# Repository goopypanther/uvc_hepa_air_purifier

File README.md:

# Air Purifier

This design was inspired by kels316's [DIY Air Purifier](https://github.com/Kels316/DIY-Air-Purifier/) and numerous other xiaomi derived air purifier designs available on thingiverse.

I didn't have easy access to the specific cylindrical HEPA filter and this design was originally intended to simply accept a different size. I went on to add UV sterilization to more closely feature-match an old commercial filtration unit which required replacement.

UV sterilization is provided by a 3W GTL3 UVC bulb which may also produce small amounts of ozone (depending on envelope coatings). This is ballasted by a capacitive dropper which provides the bulb ~10VAC at a couple hundred milliamps.

GTL3 bulbs have an interesting self-ignition design, they initially operate as a thermionic emitter using a filament with a negative thermal coefficient until a sufficient mercury plasma is generated in the envelope. The plasma cloud then conducts the majority of the current once the filament reaches a high-resistance state. AC operation is preferred over DC to prevent premature erosion of one end of the filament.

Airflow is provided by an inexpensive computer case fan operating at 12V. Due to the simplicity of the circuit and inherent safety of a fully enclosed device another capacitive dropper is used, followed by a full bridge rectifier and zener for rough regulation.

Both capacitive droppers have bleeder resistors in parallel with the class X capacitors to prevent shocks off the end of the cable. The 120VAC input is protected with a fuse, MOV and inrush current limiter. I chose to install an in-line switch into the power cable but this is optional.

In order to maximize the exposure of the air-stream to UVC radiation the area immediately surrounding the GTL3 bulb is sheathed in aluminum foil which will reflect the radiation through the chamber multiple times as well as protect the plastic from degradation. Other surfaces of the baffle are painted with white (titanium dioxide) interior house paint for protection. According to the scientific literature TiO is an efficient absorber of UVC radiation and should reduce the amount which escapes through the baffle via reflection. It also photocatalytically destroys VOCs but I'm not clear on if a paint coating has this ability or if it requires special preparation of the TiO particles.

I also posted an explanitory video of the build process [on youtube.](https://www.youtube.com/watch?v=l4DuUhZftfQ)

## File Structure

```
cad    -- FreeCAD 0.19 design documents using Assembly4 workbench
          Top level assembly document 0_top_level_uvc_air_filter.FCStd
stl    -- Exported models for 3D printing

PCB    -- Power supply PCB design files and BOM
gerber -- Zipped gerber files for PCB fabhouse
sim    -- ltspice simulation of power supply
```

## Bill Of Materials

| Qty | Part                           | Link                                                                     |
|-----|--------------------------------|--------------------------------------------------------------------------|
| 1   | PSU PCB                        | Fab from gerbers/BOM                                                     |
| 1   | Air Filter                     | https://www.amazon.com/gp/product/B08245MH67/ or similar 88mm dia filter |
| 4   | Vibration dampening fan rivets | https://www.amazon.com/gp/product/B00H9905KA/ or similar                 |
| 1   | GTL3 Bulb                      | https://www.amazon.com/gp/product/B081RSZT6S/ or similar                 |
| 1   | E17 Socket                     | https://www.amazon.com/gp/product/B07J4ZTYWZ/ or similar                 |
| 23  | M3 Nut                         | https://www.mcmaster.com/90592A085/ or similar                           |
| 21  | M3x16 Bolt                     | https://www.mcmaster.com/91290A120/ or similar                           |
| 2   | M3x8 Bolt (For E17 socket)     | https://www.mcmaster.com/91290A113/ or similar                           |
| 2   | M3 Washer (For E17 socket)     | https://www.mcmaster.com/91166a210/ or similar                           |
| 1   | Power Cable                    | https://www.mcmaster.com/7248K21/ or similar                             |
| 1   | Inline Switch (Optional)       | https://www.mcmaster.com/14695K91/ or similar                            |
| 1   | 120mm Fan                      | Purchase or recycle from PC                                              |
| 1   | Aluminum Foil                  | Purchase                                                                 |
| 2   | Zipties (For Power Cable)      | Purchase                                                                 |
| 4   | M3x5 Standoff                  | 3D Print or purchase                                                     |
| 3   | Foot                           | 3D Print in TPU or purchase compatible feet                              |
| 1   | Upper Baffle                   | 3D Print                                                                 |
| 1   | Top Cap                        | 3D Print                                                                 |
| 1   | Lower Baffle                   | 3D Print                                                                 |
| 1   | Fan Cover                      | 3D Print                                                                 |
| 1   | Bottom Cap                     | 3D Print                                                                 |
| 1   | Baffle Cap Bracket             | 3D Print                                                                 |
| 1   | Baffle Cap                     | 3D Print                                                                 |

## Assembly Notes

The supplied gerber zip file is submittable to JLCPCB/OSHPARK or other PCB fabhouse. It is important that the AC series capacitors are at least class X1 to prevent blown fuses or fire. Take care when testing this circuit, the outputs float and may have a 120VAC potential to ground so don't touch it! It may also destroy non-isolated oscilloscopes or other ground-referenced test equipment. UVC light is dangerous to the eyes and causes skin cancer, damages plastic and will even kill houseplants with sufficient exposure. Don't stare at the bulb, only run open-air tests briefly and preferably view it through the screen of a digital camera or UV filtered glasses.

Total 3D printing time on my ender 3 with 20% infill was about 75 hours and used approximately 500g of filament.

Coat innermost surfaces of Bottom Cap with TiO paint, as well as outer surfaces of Upper and Lower Baffle and inner surfaces of Baffle Cap.

For ease of construction build the Internal Baffle Assembly first and glue aluminum foil to its inner surface. Then assemble into Top Cap.

Build Bottom Cap Assembly and Fan Cover Assembly as independent units. Ensure fan blows air outward through the vent holes. When screwing feet into Bottom Cap ensure the bolts do not sit excessively proud of the Bottom Cap surface where they would interfere with the filter's foam seal.

When building Baffle Cap Assembly start by installing the Baffle Cap Bracket, then the E17 Socket. The E17 mounting holes were oversized and required washers. Feed E17 wires through the holes in the Baffle Cap and Bracket before installing fasteners. Use short bolts to leave room on rear face for the PCB. The two captive nut features on the top face of the Baffle Cap were tight but the nuts seated as the bolts were screwed in. Afterward the PCB can be installed with the standoffs and the E17 wires can be connected. At that point the GTL3 bulb can be screwed into the socket and the assembly can be attached to the Top Cap.

For stability the Bottom Cap Assembly, Filter and Top Cap Assembly can be fit together before wiring the Power Cable. Plug the fan into the PCB and carefully slot the power cable into the mouse-hole on the edge of the Fan Cover. With the Fan Cover seated over the Top Cap a ziptie can be applied to the cable up against the cover to prevent it from being pushed inside the unit. The Fan Cover can then be temporarily removed to install a second ziptie on the cable against the inner surface of the Fan Cover to prevent the cable from being pulled out of the PCB. The Fan Cover can then be screwed into the Top Cap taking care that the bolts do not sit excessively proud of the surface where they would interfere with the filter's foam seal.

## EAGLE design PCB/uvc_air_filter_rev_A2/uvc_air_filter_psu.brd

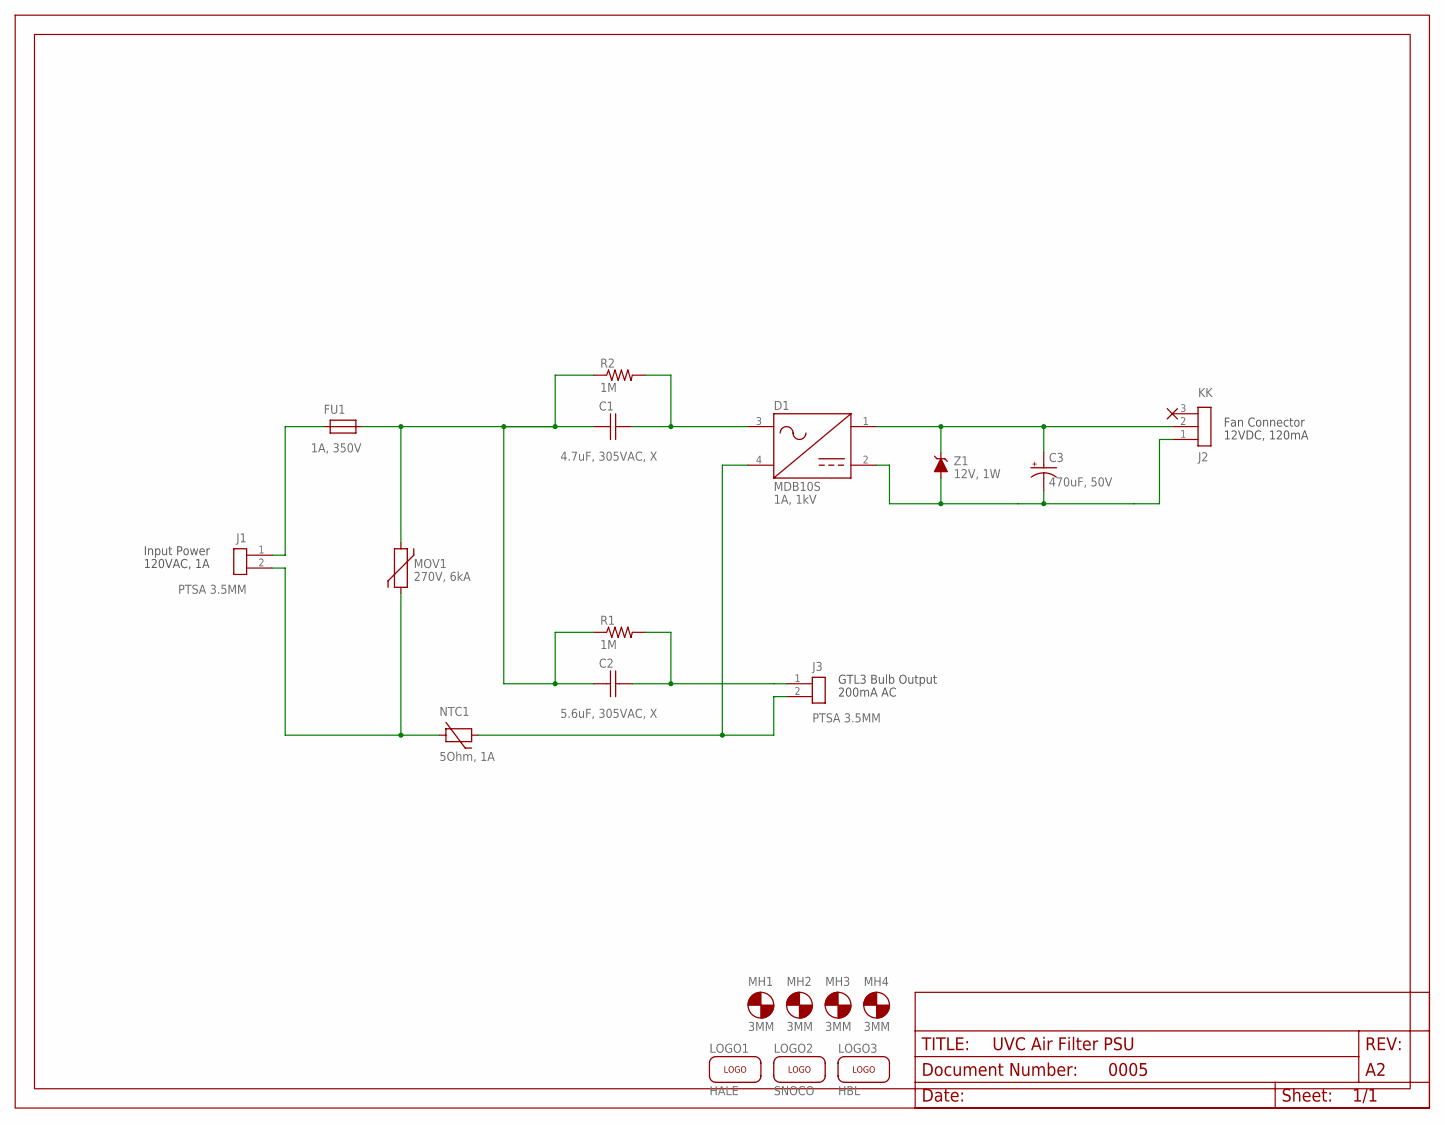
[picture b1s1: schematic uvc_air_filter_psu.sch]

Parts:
C1: 4.7uF, 305VAC, X; CAP-27.5MM
C2: 5.6uF, 305VAC, X; CAP-27.5MM
C3: 470uF, 50V; CAP-5MM-10MM; DIGIKEY P5185-ND
D1: 1A, 1kV; TSSOP-4
FU1: 1A, 350V; FUSE-5X15MM
J1, J3: PTSA 3.5MM; HEADER-PTSA-3.5MM-1X2
J2: KK; HEADER-KK-1X3
LOGO1: HALE; HALE-SILK-ICON
LOGO2: SNOCO; SNOCO-SILK-ICON
LOGO3: HBL; HACKERBOT-SILK-ICON
MH1, MH2, MH3, MH4: 3MM; MH-M3
MOV1: 270V, 6kA; MOV-B722-7.5MM
NTC1: 5Ohm, 1A; MF72-D5-NTC
R1, R2: 1M; 1206-NONPOLAR; DIGIKEY 311-1.00MFRCT-ND
U$1: FRAME-8.5X11-LANDSCAPE-LET; FRAME-8.5X11-LANDSCAPE
Z1: 12V, 1W; SMA

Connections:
unnamed: FU1.1, J1.1
unnamed: C1.2 (-), D1.3 (1), R2.2
unnamed: C1.1 (+), C2.1 (+), FU1.2, MOV1.1, R1.1, R2.1
unnamed: C2.2 (-), J3.1, R1.2
unnamed: C3.2 (-), D1.2 (-), J2.1, Z1.1 (A)
unnamed: C3.1 (+), D1.1 (+), J2.2, Z1.2 (C)
unnamed: D1.4 (2), J3.2, NTC1.2
unnamed: J1.2, MOV1.2, NTC1.1

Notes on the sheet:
12VDC, 120mA
Fan Connector
GTL3 Bulb Output
200mA AC
Input Power
120VAC, 1A

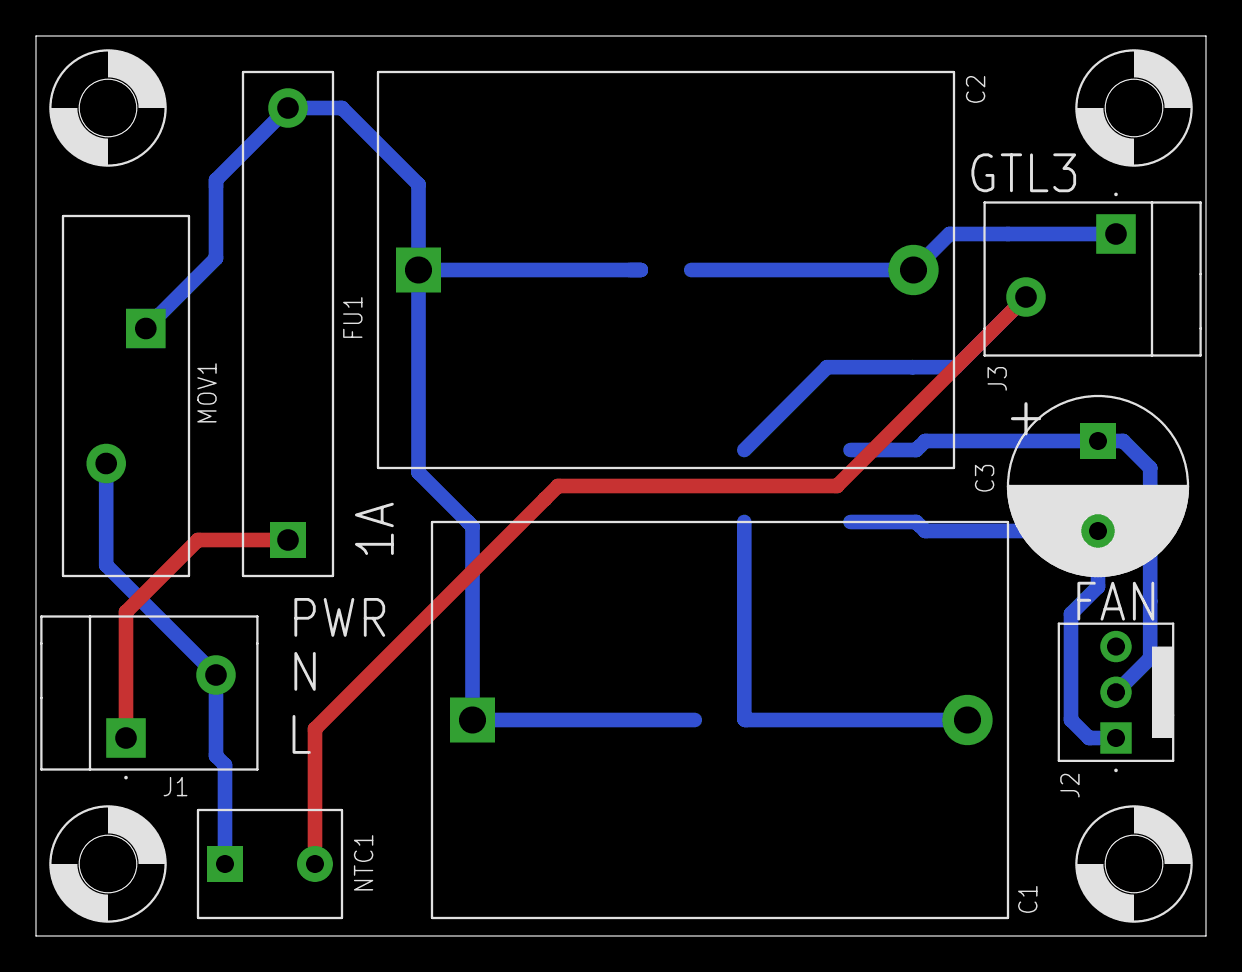
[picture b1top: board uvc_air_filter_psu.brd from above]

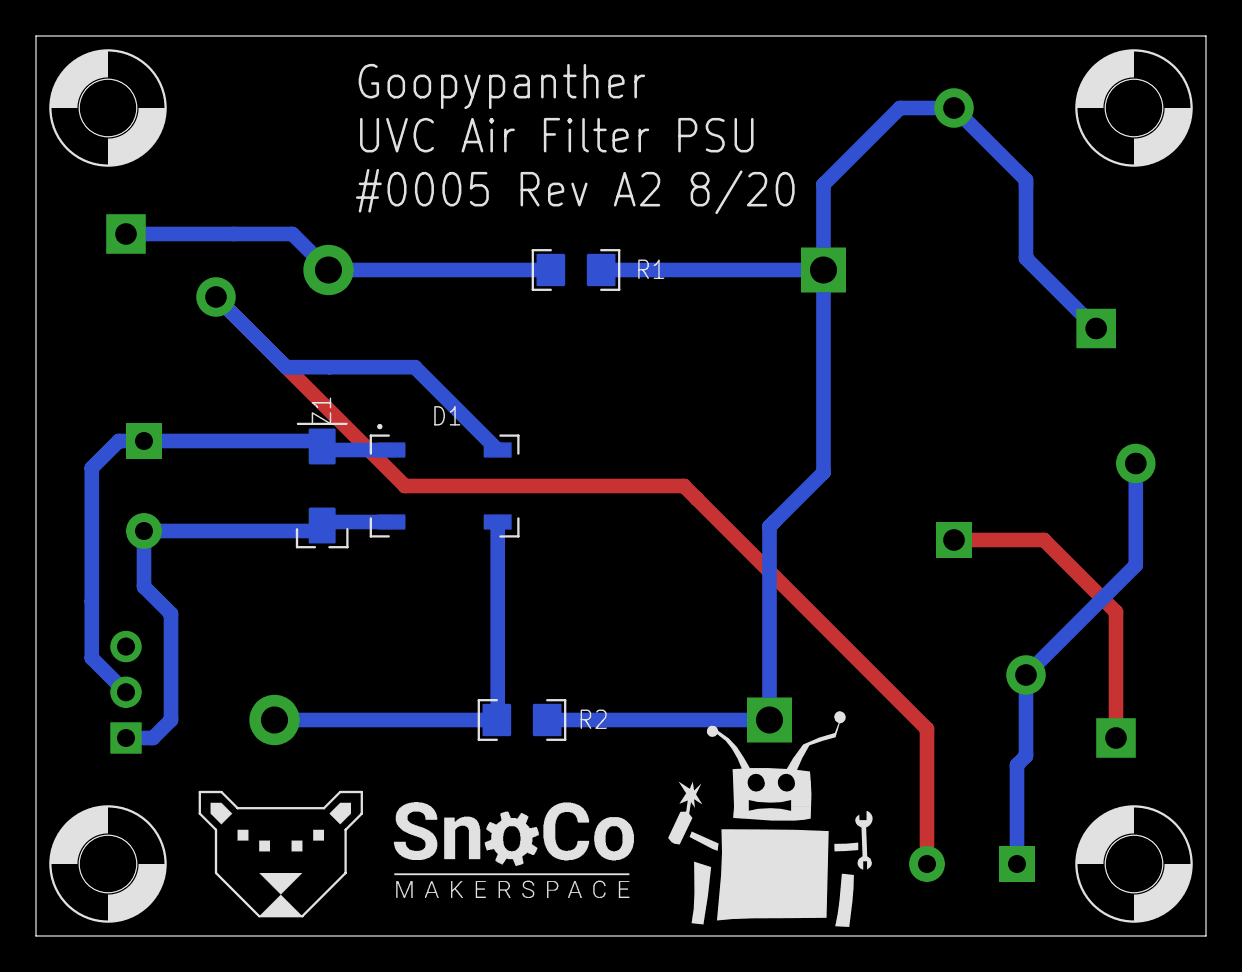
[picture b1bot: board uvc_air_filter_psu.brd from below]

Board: 2 copper layers, 65.0 x 50.0 mm, 22 parts (7 on the bottom side), 8 nets.

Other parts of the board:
DRILEGEND: DRILEGEND

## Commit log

2020-08-20 Initial
2020-08-20 edit
2020-10-07 Add youtube link
2020-10-07 fix newline
